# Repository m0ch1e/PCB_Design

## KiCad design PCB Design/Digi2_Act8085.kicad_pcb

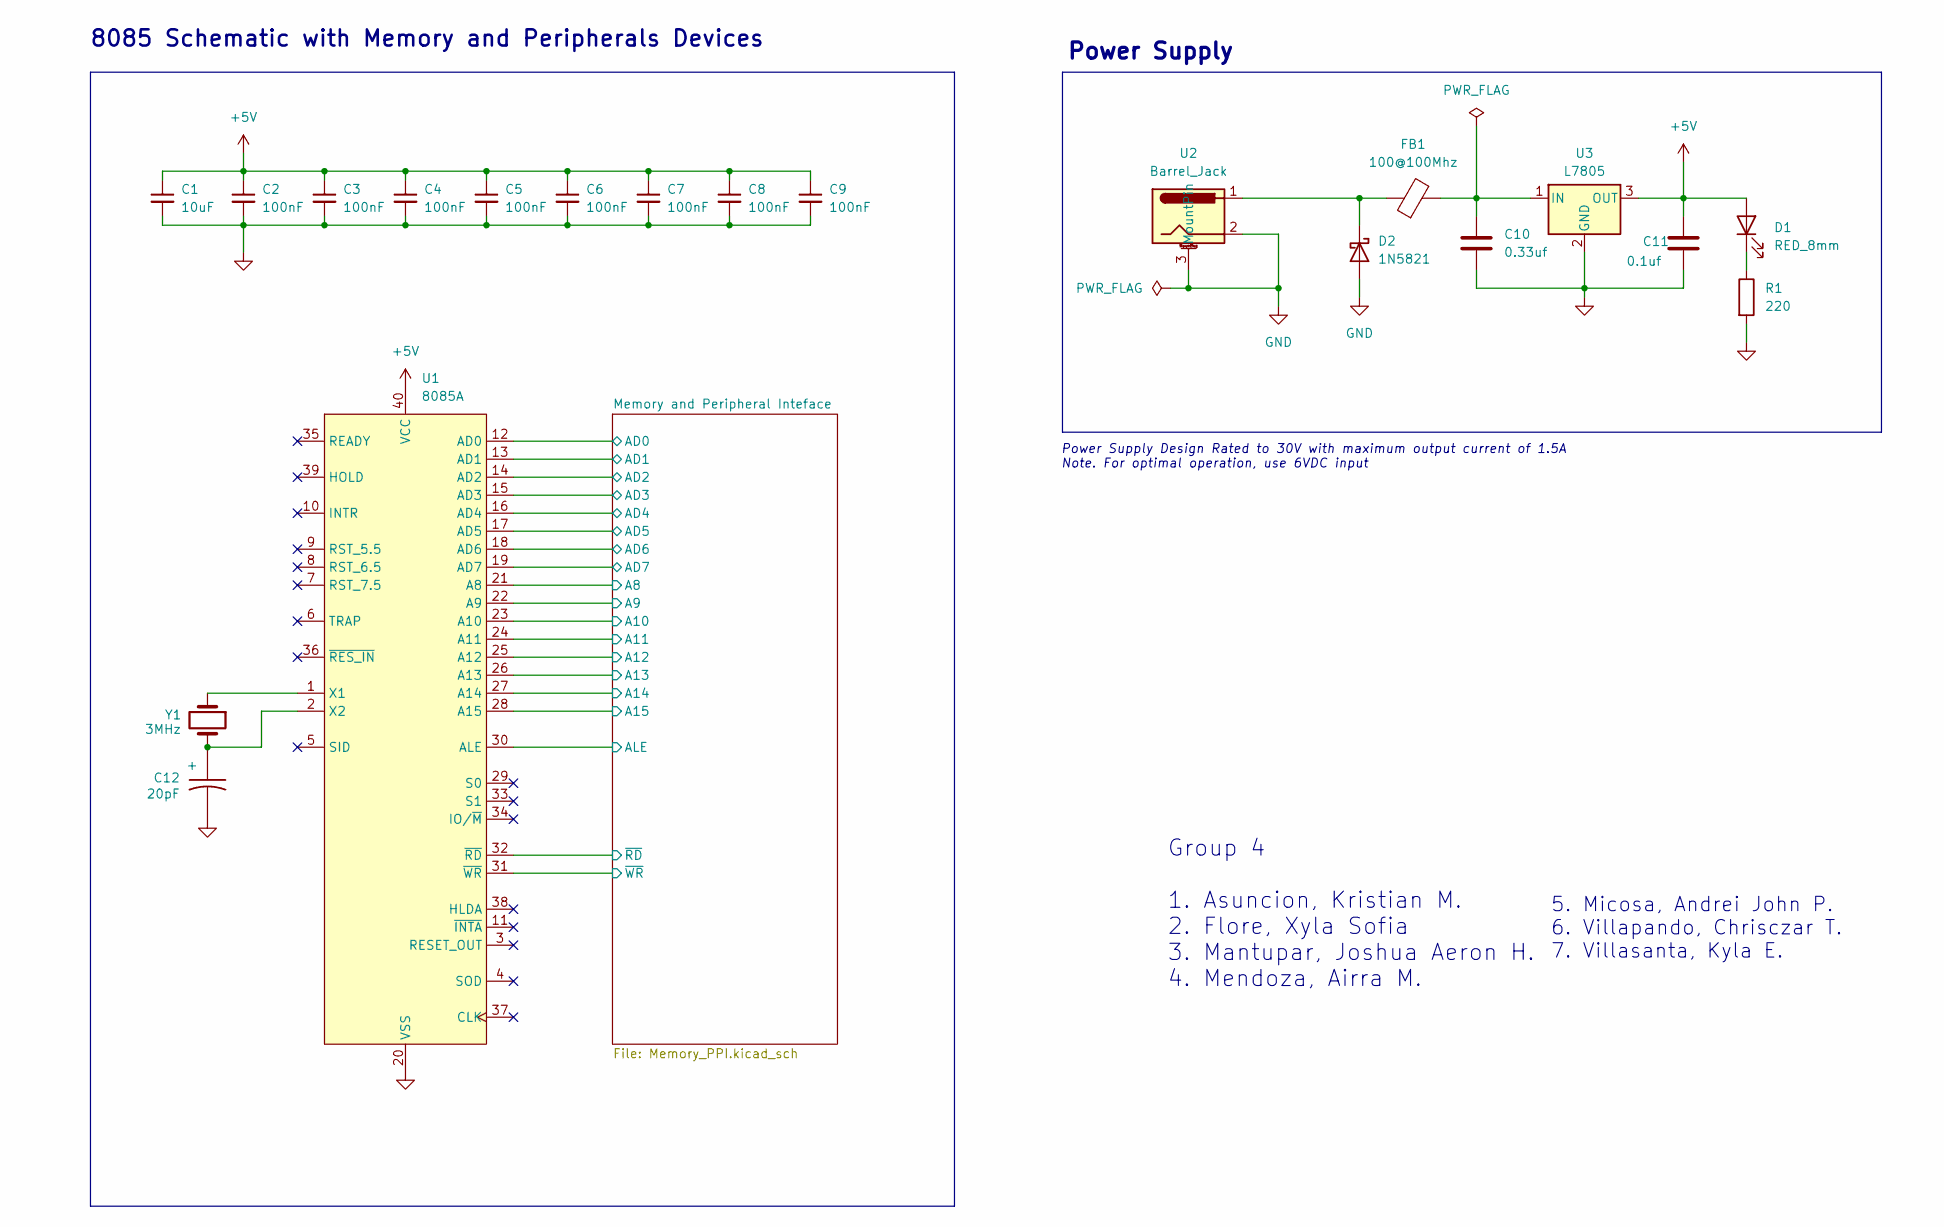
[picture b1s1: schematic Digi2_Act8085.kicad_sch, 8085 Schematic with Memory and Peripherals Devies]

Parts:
C1: 10uF; CP_Radial_D8.0mm_P3.50mm
C2, C3, C4, C5, C6, C7, C8, C9: 100nF; C_Disc_D4.3mm_W1.9mm_P5.00mm
C10: 0.33uf; CP_Radial_D8.0mm_P3.50mm
C11: 0.1uf; CP_Radial_D8.0mm_P3.50mm
C12: 20pF; CP_Radial_D5.0mm_P2.50mm
D1: RED_8mm; LED_D8.0mm
D2: 1N5821; D_DO-201AD_P15.24mm_Horizontal
FB1: 100@100Mhz; LairdTech_28C0236-0JW-10
R1: 220; R_Axial_DIN0207_L6.3mm_D2.5mm_P7.62mm_Horizontal
U1: 8085A; DIP-40_W15.24mm
U2: Barrel_Jack; BarrelJack_Horizontal
U3: L7805; TO-220-3_Vertical
Y1: 3MHz; Crystal_HC49-U_Vertical

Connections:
+5V: C1.1, C2.1, C3.1, C4.1, C5.1, C6.1, C7.1, C8.1, C9.1, C11.1, D1.2 (A), U1.40 (VCC), U3.3 (OUT); also elsewhere on the board
/Memory and Peripheral Inteface/A8: U1.21 (A8); also elsewhere on the board
/Memory and Peripheral Inteface/A9: U1.22 (A9); also elsewhere on the board
/Memory and Peripheral Inteface/A10: U1.23 (A10); also elsewhere on the board
/Memory and Peripheral Inteface/A11: U1.24 (A11); also elsewhere on the board
/Memory and Peripheral Inteface/A12: U1.25 (A12); also elsewhere on the board
/Memory and Peripheral Inteface/A13: U1.26 (A13); also elsewhere on the board
/Memory and Peripheral Inteface/A14: U1.27 (A14); also elsewhere on the board
/Memory and Peripheral Inteface/A15: U1.28 (A15); also elsewhere on the board
/Memory and Peripheral Inteface/AD0: U1.12 (AD0); also elsewhere on the board
/Memory and Peripheral Inteface/AD1: U1.13 (AD1); also elsewhere on the board
/Memory and Peripheral Inteface/AD2: U1.14 (AD2); also elsewhere on the board
/Memory and Peripheral Inteface/AD3: U1.15 (AD3); also elsewhere on the board
/Memory and Peripheral Inteface/AD4: U1.16 (AD4); also elsewhere on the board
/Memory and Peripheral Inteface/AD5: U1.17 (AD5); also elsewhere on the board
/Memory and Peripheral Inteface/AD6: U1.18 (AD6); also elsewhere on the board
/Memory and Peripheral Inteface/AD7: U1.19 (AD7); also elsewhere on the board
/Memory and Peripheral Inteface/ALE: U1.30 (ALE); also elsewhere on the board
/Memory and Peripheral Inteface/~RD: U1.32 (~RD); also elsewhere on the board
/Memory and Peripheral Inteface/~WR: U1.31 (~WR); also elsewhere on the board
GND: C1.2, C2.2, C3.2, C4.2, C5.2, C6.2, C7.2, C8.2, C9.2, C10.2, C11.2, C12.2 (-), D2.2 (A), R1.2, U1.20 (VSS), U2.2, U2.3 (MountPin), U3.2 (GND); also elsewhere on the board
unnamed: C12.1 (+), U1.2 (X2), Y1.2
unnamed: D1.1 (K), R1.1
unnamed: D2.1 (K), FB1.1, U2.1
unnamed: U1.1 (X1), Y1.1
unnamed: C10.1, FB1.2, U3.1 (IN)

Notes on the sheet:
Power Supply Design Rated to 30V with maximum output current of 1.5A Note. For optimal operation, use 6VDC input
Group 4 1. Asuncion, Kristian M. 2. Flore, Xyla Sofia 3. Mantupar, Joshua Aeron H. 4. Mendoza, Airra M.
Power Supply
5. Micosa, Andrei John P. 6. Villapando, Chrisczar T. 7. Villasanta, Kyla E.
8085 Schematic with Memory and Peripherals Devices

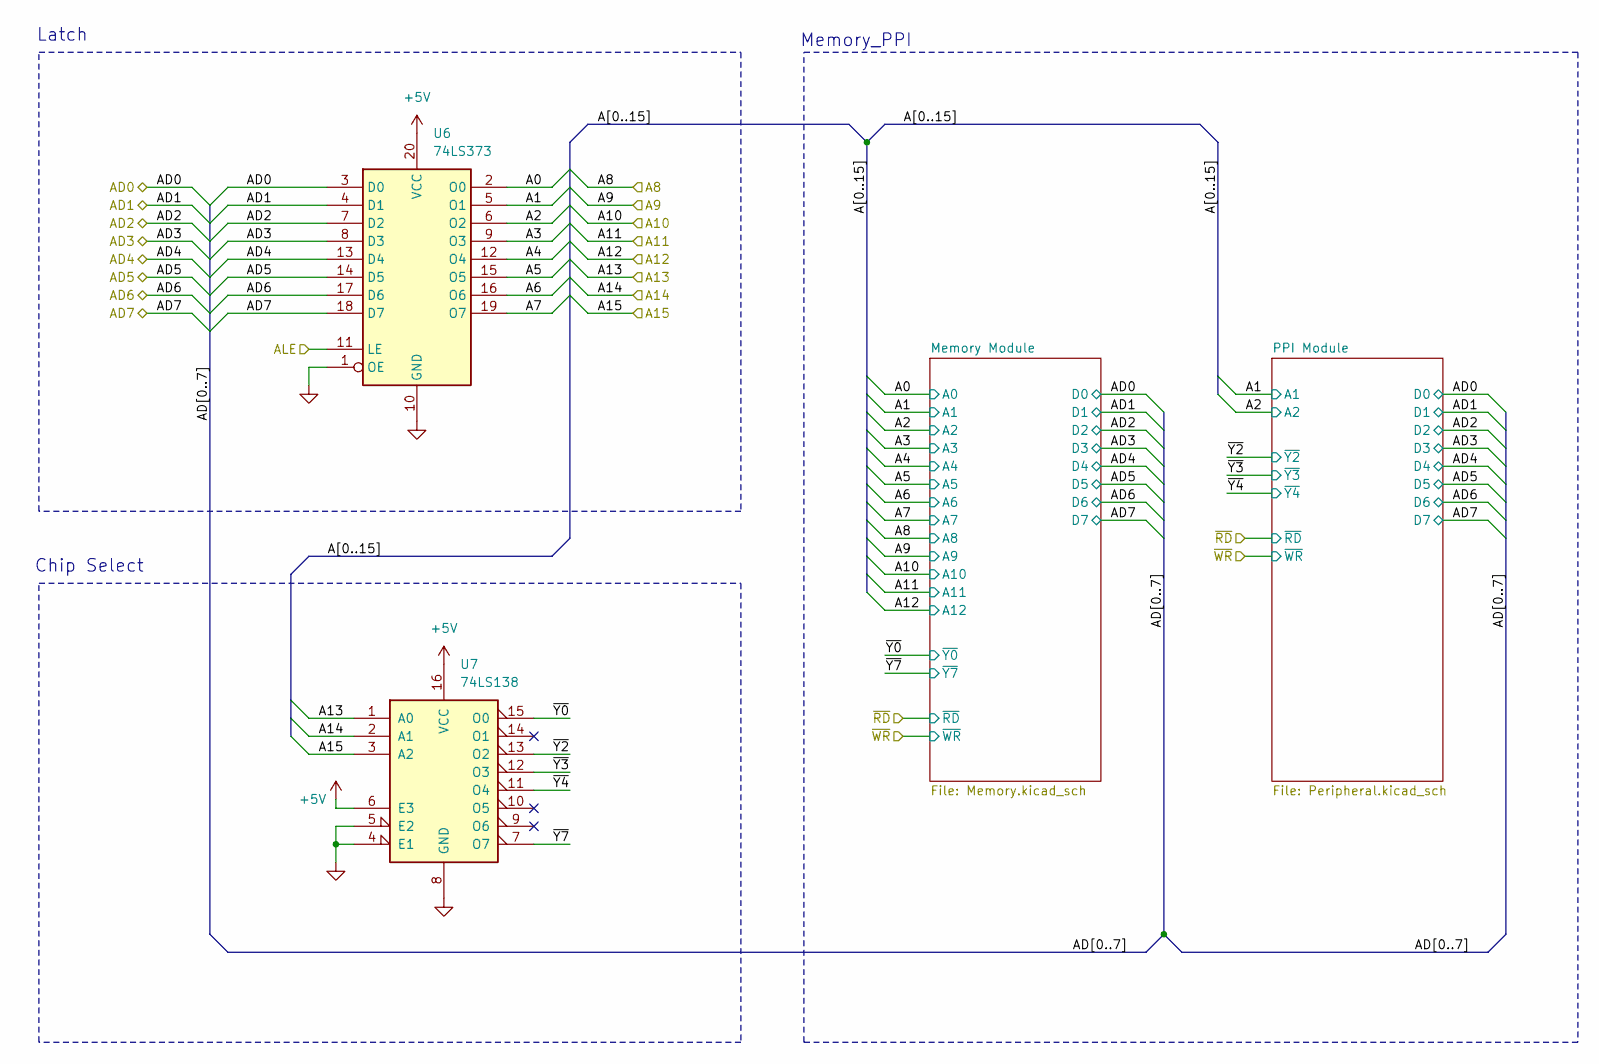
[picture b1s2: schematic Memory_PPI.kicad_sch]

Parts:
U6: 74LS373; DIP-20_W7.62mm
U7: 74LS138; DIP-16_W7.62mm

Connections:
+5V: U6.20 (VCC), U7.6 (E3), U7.16 (VCC); also elsewhere on the board
/Memory and Peripheral Inteface/A0: U6.2 (O0); also elsewhere on the board
/Memory and Peripheral Inteface/A1: U6.5 (O1); also elsewhere on the board
/Memory and Peripheral Inteface/A2: U6.6 (O2); also elsewhere on the board
/Memory and Peripheral Inteface/A3: U6.9 (O3); also elsewhere on the board
/Memory and Peripheral Inteface/A4: U6.12 (O4); also elsewhere on the board
/Memory and Peripheral Inteface/A5: U6.15 (O5); also elsewhere on the board
/Memory and Peripheral Inteface/A6: U6.16 (O6); also elsewhere on the board
/Memory and Peripheral Inteface/A7: U6.19 (O7); also elsewhere on the board
/Memory and Peripheral Inteface/A13: U7.1 (A0); also elsewhere on the board
/Memory and Peripheral Inteface/A14: U7.2 (A1); also elsewhere on the board
/Memory and Peripheral Inteface/A15: U7.3 (A2); also elsewhere on the board
/Memory and Peripheral Inteface/AD0: U6.3 (D0); also elsewhere on the board
/Memory and Peripheral Inteface/AD1: U6.4 (D1); also elsewhere on the board
/Memory and Peripheral Inteface/AD2: U6.7 (D2); also elsewhere on the board
/Memory and Peripheral Inteface/AD3: U6.8 (D3); also elsewhere on the board
/Memory and Peripheral Inteface/AD4: U6.13 (D4); also elsewhere on the board
/Memory and Peripheral Inteface/AD5: U6.14 (D5); also elsewhere on the board
/Memory and Peripheral Inteface/AD6: U6.17 (D6); also elsewhere on the board
/Memory and Peripheral Inteface/AD7: U6.18 (D7); also elsewhere on the board
/Memory and Peripheral Inteface/ALE: U6.11 (LE); also elsewhere on the board
/Memory and Peripheral Inteface/~Y0: U7.15 (O0); also elsewhere on the board
/Memory and Peripheral Inteface/~Y2: U7.13 (O2); also elsewhere on the board
/Memory and Peripheral Inteface/~Y3: U7.12 (O3); also elsewhere on the board
/Memory and Peripheral Inteface/~Y4: U7.11 (O4); also elsewhere on the board
/Memory and Peripheral Inteface/~Y7: U7.7 (O7); also elsewhere on the board
GND: U6.1 (OE), U6.10 (GND), U7.4 (E1), U7.5 (E2), U7.8 (GND); also elsewhere on the board

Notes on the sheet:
Chip Select
Memory_PPI
Latch

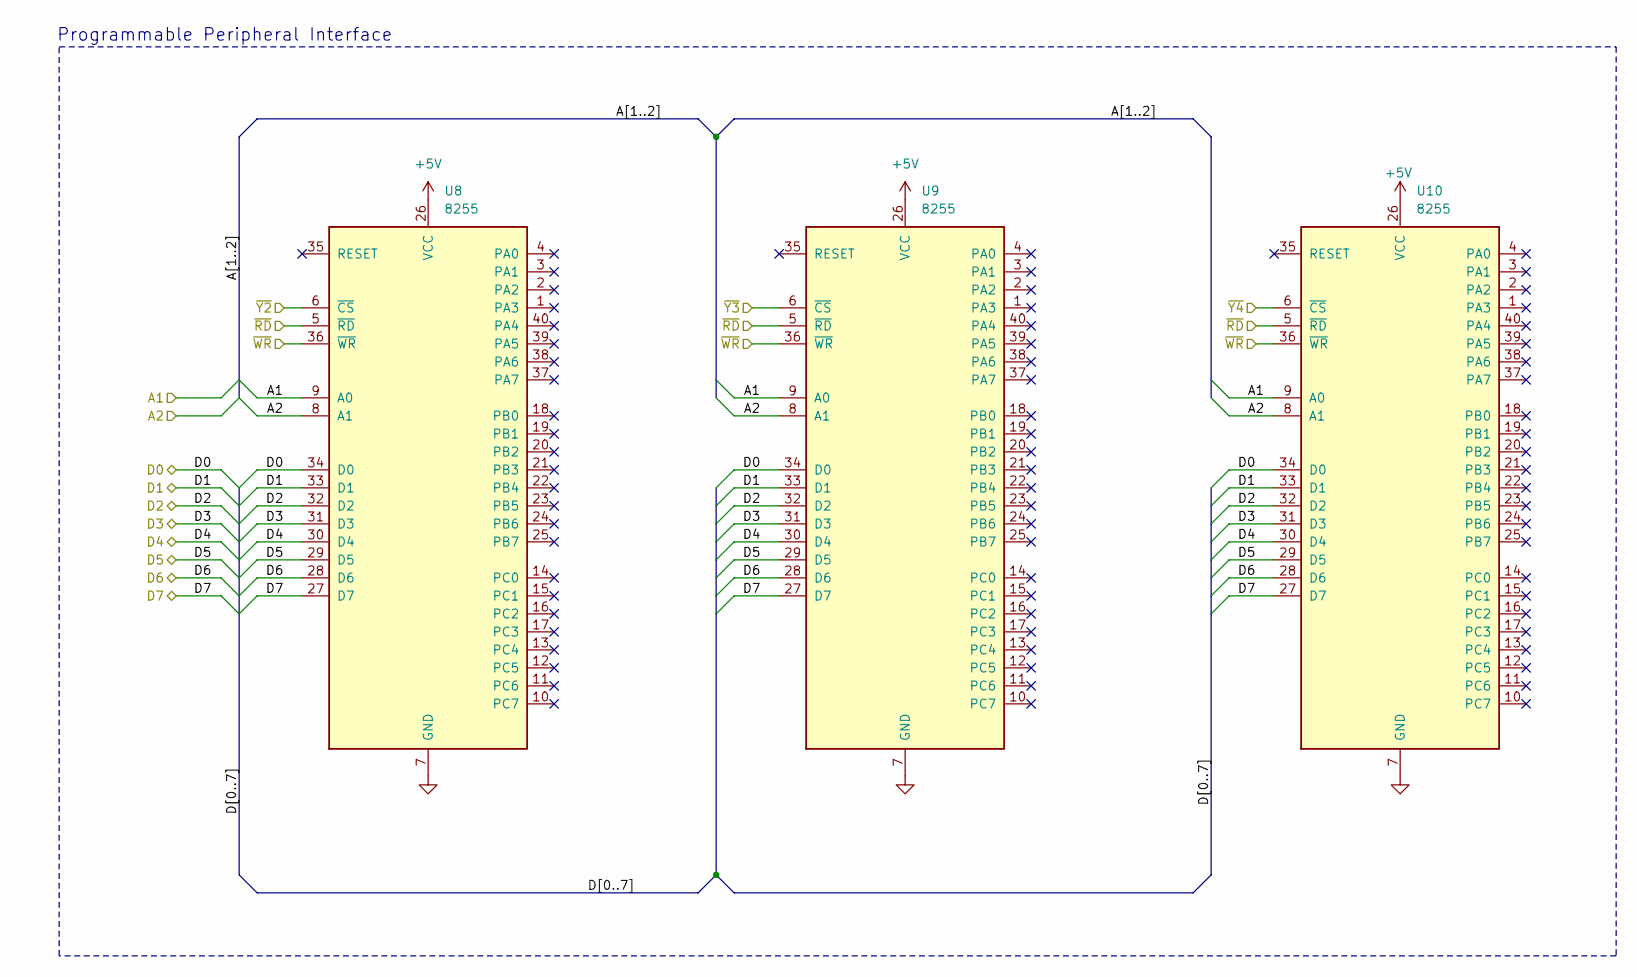
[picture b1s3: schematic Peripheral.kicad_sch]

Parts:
U8, U9, U10: 8255; DIP-40_W15.24mm

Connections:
+5V: U8.26 (VCC), U9.26 (VCC), U10.26 (VCC); also elsewhere on the board
/Memory and Peripheral Inteface/A1: U8.9 (A0), U9.9 (A0), U10.9 (A0); also elsewhere on the board
/Memory and Peripheral Inteface/A2: U8.8 (A1), U9.8 (A1), U10.8 (A1); also elsewhere on the board
/Memory and Peripheral Inteface/AD0: U8.34 (D0), U9.34 (D0), U10.34 (D0); also elsewhere on the board
/Memory and Peripheral Inteface/AD1: U8.33 (D1), U9.33 (D1), U10.33 (D1); also elsewhere on the board
/Memory and Peripheral Inteface/AD2: U8.32 (D2), U9.32 (D2), U10.32 (D2); also elsewhere on the board
/Memory and Peripheral Inteface/AD3: U8.31 (D3), U9.31 (D3), U10.31 (D3); also elsewhere on the board
/Memory and Peripheral Inteface/AD4: U8.30 (D4), U9.30 (D4), U10.30 (D4); also elsewhere on the board
/Memory and Peripheral Inteface/AD5: U8.29 (D5), U9.29 (D5), U10.29 (D5); also elsewhere on the board
/Memory and Peripheral Inteface/AD6: U8.28 (D6), U9.28 (D6), U10.28 (D6); also elsewhere on the board
/Memory and Peripheral Inteface/AD7: U8.27 (D7), U9.27 (D7), U10.27 (D7); also elsewhere on the board
/Memory and Peripheral Inteface/~RD: U8.5 (~RD), U9.5 (~RD), U10.5 (~RD); also elsewhere on the board
/Memory and Peripheral Inteface/~WR: U8.36 (~WR), U9.36 (~WR), U10.36 (~WR); also elsewhere on the board
/Memory and Peripheral Inteface/~Y2: U8.6 (~CS); also elsewhere on the board
/Memory and Peripheral Inteface/~Y3: U9.6 (~CS); also elsewhere on the board
/Memory and Peripheral Inteface/~Y4: U10.6 (~CS); also elsewhere on the board
GND: U8.7 (GND), U9.7 (GND), U10.7 (GND); also elsewhere on the board

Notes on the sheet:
Programmable Peripheral Interface

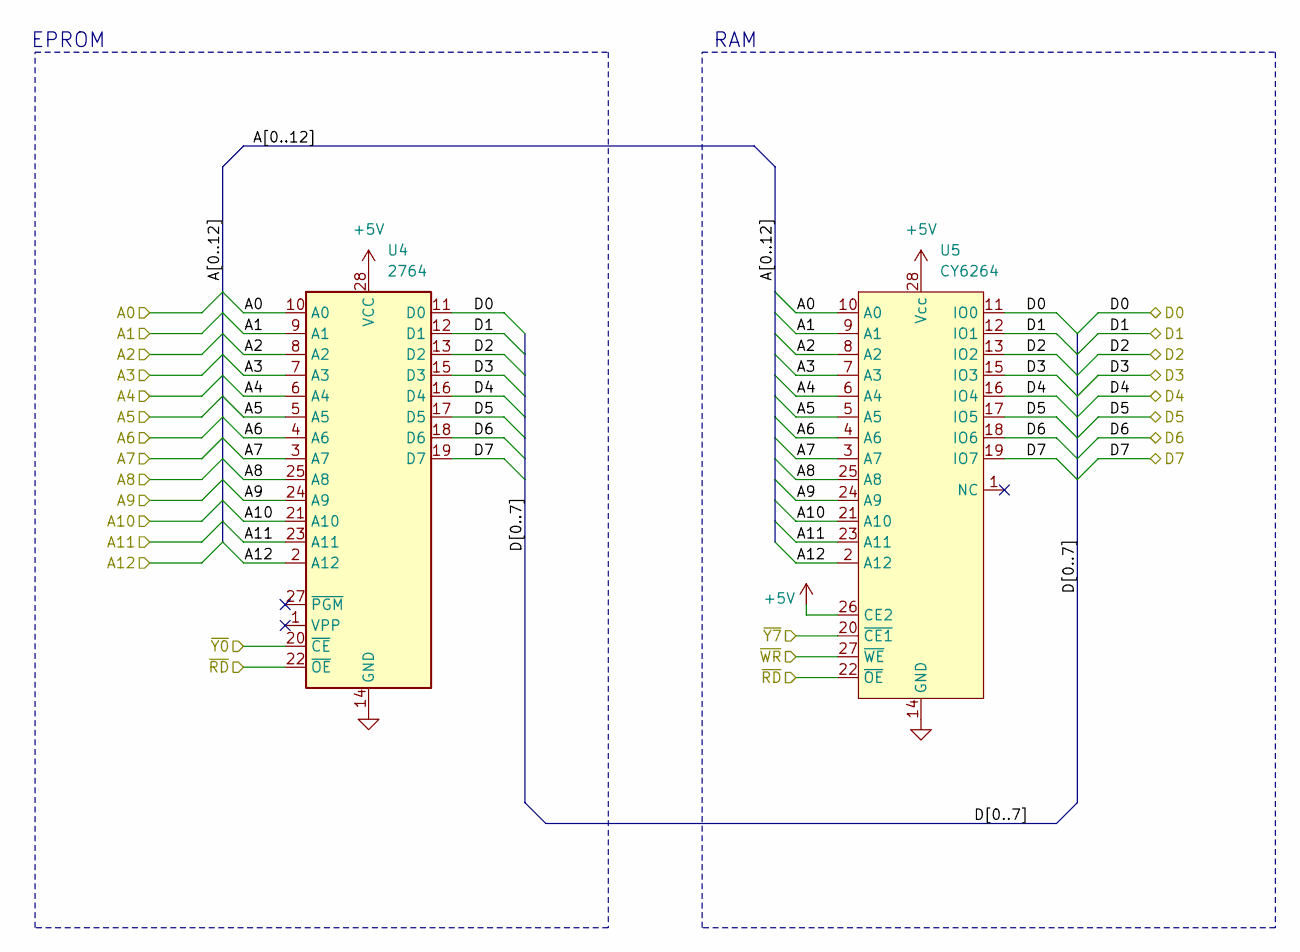
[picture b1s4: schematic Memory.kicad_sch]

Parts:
U4: 2764; DIP-28_W15.24mm
U5: CY6264; DIP-28_W15.24mm

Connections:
+5V: U4.28 (VCC), U5.26 (CE2), U5.28 (Vcc); also elsewhere on the board
/Memory and Peripheral Inteface/A0: U4.10 (A0), U5.10 (A0); also elsewhere on the board
/Memory and Peripheral Inteface/A1: U4.9 (A1), U5.9 (A1); also elsewhere on the board
/Memory and Peripheral Inteface/A2: U4.8 (A2), U5.8 (A2); also elsewhere on the board
/Memory and Peripheral Inteface/A3: U4.7 (A3), U5.7 (A3); also elsewhere on the board
/Memory and Peripheral Inteface/A4: U4.6 (A4), U5.6 (A4); also elsewhere on the board
/Memory and Peripheral Inteface/A5: U4.5 (A5), U5.5 (A5); also elsewhere on the board
/Memory and Peripheral Inteface/A6: U4.4 (A6), U5.4 (A6); also elsewhere on the board
/Memory and Peripheral Inteface/A7: U4.3 (A7), U5.3 (A7); also elsewhere on the board
/Memory and Peripheral Inteface/A8: U4.25 (A8), U5.25 (A8); also elsewhere on the board
/Memory and Peripheral Inteface/A9: U4.24 (A9), U5.24 (A9); also elsewhere on the board
/Memory and Peripheral Inteface/A10: U4.21 (A10), U5.21 (A10); also elsewhere on the board
/Memory and Peripheral Inteface/A11: U4.23 (A11), U5.23 (A11); also elsewhere on the board
/Memory and Peripheral Inteface/A12: U4.2 (A12), U5.2 (A12); also elsewhere on the board
/Memory and Peripheral Inteface/AD0: U4.11 (D0), U5.11 (IO0); also elsewhere on the board
/Memory and Peripheral Inteface/AD1: U4.12 (D1), U5.12 (IO1); also elsewhere on the board
/Memory and Peripheral Inteface/AD2: U4.13 (D2), U5.13 (IO2); also elsewhere on the board
/Memory and Peripheral Inteface/AD3: U4.15 (D3), U5.15 (IO3); also elsewhere on the board
/Memory and Peripheral Inteface/AD4: U4.16 (D4), U5.16 (IO4); also elsewhere on the board
/Memory and Peripheral Inteface/AD5: U4.17 (D5), U5.17 (IO5); also elsewhere on the board
/Memory and Peripheral Inteface/AD6: U4.18 (D6), U5.18 (IO6); also elsewhere on the board
/Memory and Peripheral Inteface/AD7: U4.19 (D7), U5.19 (IO7); also elsewhere on the board
/Memory and Peripheral Inteface/~RD: U4.22 (~OE), U5.22 (~OE); also elsewhere on the board
/Memory and Peripheral Inteface/~WR: U5.27 (~WE); also elsewhere on the board
/Memory and Peripheral Inteface/~Y0: U4.20 (~CE); also elsewhere on the board
/Memory and Peripheral Inteface/~Y7: U5.20 (~CE1); also elsewhere on the board
GND: U4.14 (GND), U5.14 (GND); also elsewhere on the board

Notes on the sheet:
EPROM
RAM

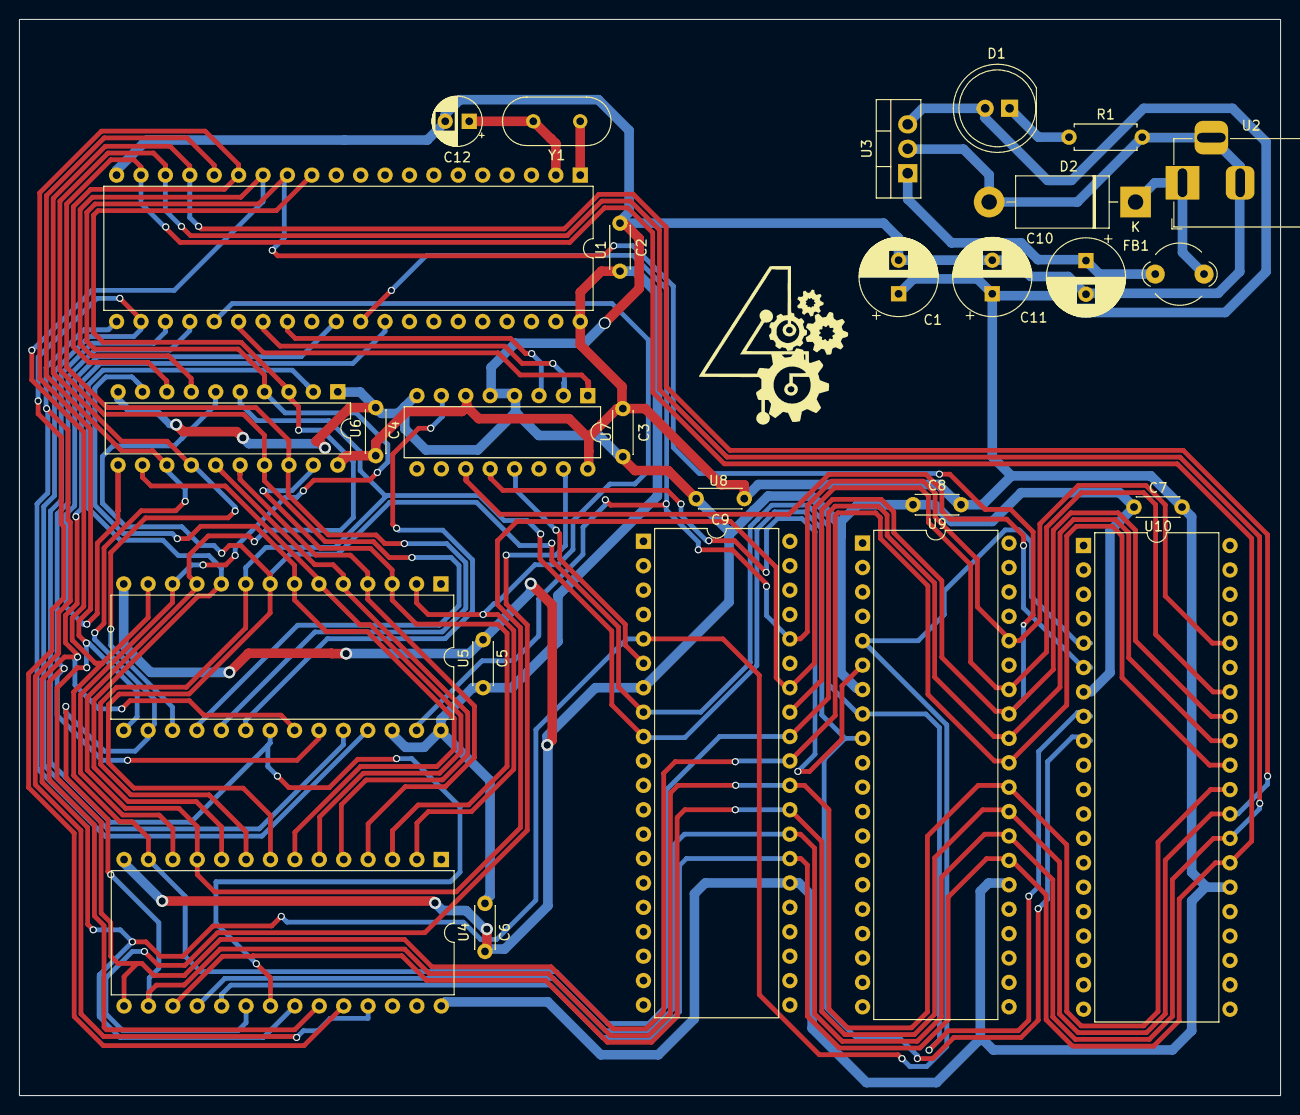
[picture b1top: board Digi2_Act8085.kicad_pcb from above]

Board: 2 copper layers, 131.2 x 112.0 mm, 27 parts (0 on the bottom side), 39 nets.

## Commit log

2024-05-18 Initial
2024-05-18 Board Layout
2024-05-18 New Board Layout
2024-05-18 Initial B
2024-05-18 Set Pre defined width
2024-05-18 Route 8085->Multiplexer
2024-05-18 power supply routing
2024-05-18 Peripheral Routing
2024-05-18 Additional Route
2024-05-18 Test C merge A
2024-05-18 copy of main
2024-05-18 copy of main(1)
2024-05-18 test merge D
2024-05-18 test merge3
2024-05-18 updated p
2024-05-18 test
2024-05-18 test2
2024-05-18 test3
2024-05-18 test4
2024-05-18 test5
2024-05-18 test6
2024-05-18 testxxx
2024-05-18 testfxfx
2024-05-18 kahit ano
2024-05-18 newwwwwwwwwwwwwwwwww
2024-05-18 newwwwwwwwww
2024-05-18 newwwwwwwwwwww
2024-05-19 dizshitz
